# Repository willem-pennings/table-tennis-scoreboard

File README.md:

# Table tennis scoreboard
Hardware and software design for an electronic table tennis score board.

## Features
This device has the following characteristics:
- Keeps track of scores, number of games, and timeouts.
- Remotely controlled using Wi-Fi and a web server.
- A mechanical design which is mainly based on laser-cut parts.
- WS2813 LEDs: adjustable screen colour and brightness.
- Software runs on an ESP32-S3.

## Building it
Mechanical parts are laser-cut from sheet material. An overview of individual parts:
- [Perspex Frost Midnight Black 9221, 3 mm thickness](https://www.laserbeest.nl/materialen/acrylaat-zwart-frost-3mm/)
  - ``front.svg``
  - ``back.svg``
  - ``wall-side-no-holes.svg``
  - ``wall-side-with-holes.svg``
  - ``wall-top-bottom.svg``
- [Perspex Frost Slate Grey 9T23, 3 mm thickness](https://www.laserbeest.nl/materialen/acrylaat-frost-donkergrijs-3-mm/)
  - ``diffuser-major.svg``
  - ``diffuser-minor.svg``
  - ``diffuser-timeout.svg``
- [PE rigid foam, 20 mm thickness](https://snijlab.nl/en/products/pe-rigid-foam?variant=48708138500423)
  - ``lightbox.svg``

Production files have also been prepared which can be sent to Dutch lasercutting companies as-is:
 - ``mechanical/production/production-laserbeest.pdf``
 - ``mechanical/production/production-snijlab.pdf``

The following additional parts are required to assemble the enclosure:
- 50x ISO7380 screw, M3x10.
- 15x M3x50 standoff, fully threaded, black ([example](https://www.aliexpress.com/item/1005004063804402.html)).
- 15x M3x20 standoff, fully threaded ([example](https://www.aliexpress.com/item/4000152799825.html)).
- USB type C extension cable ([example](https://www.aliexpress.com/item/1005005446667716.html)).
- Cyanoacrylate glue to join the frosted diffusers to the front plate.

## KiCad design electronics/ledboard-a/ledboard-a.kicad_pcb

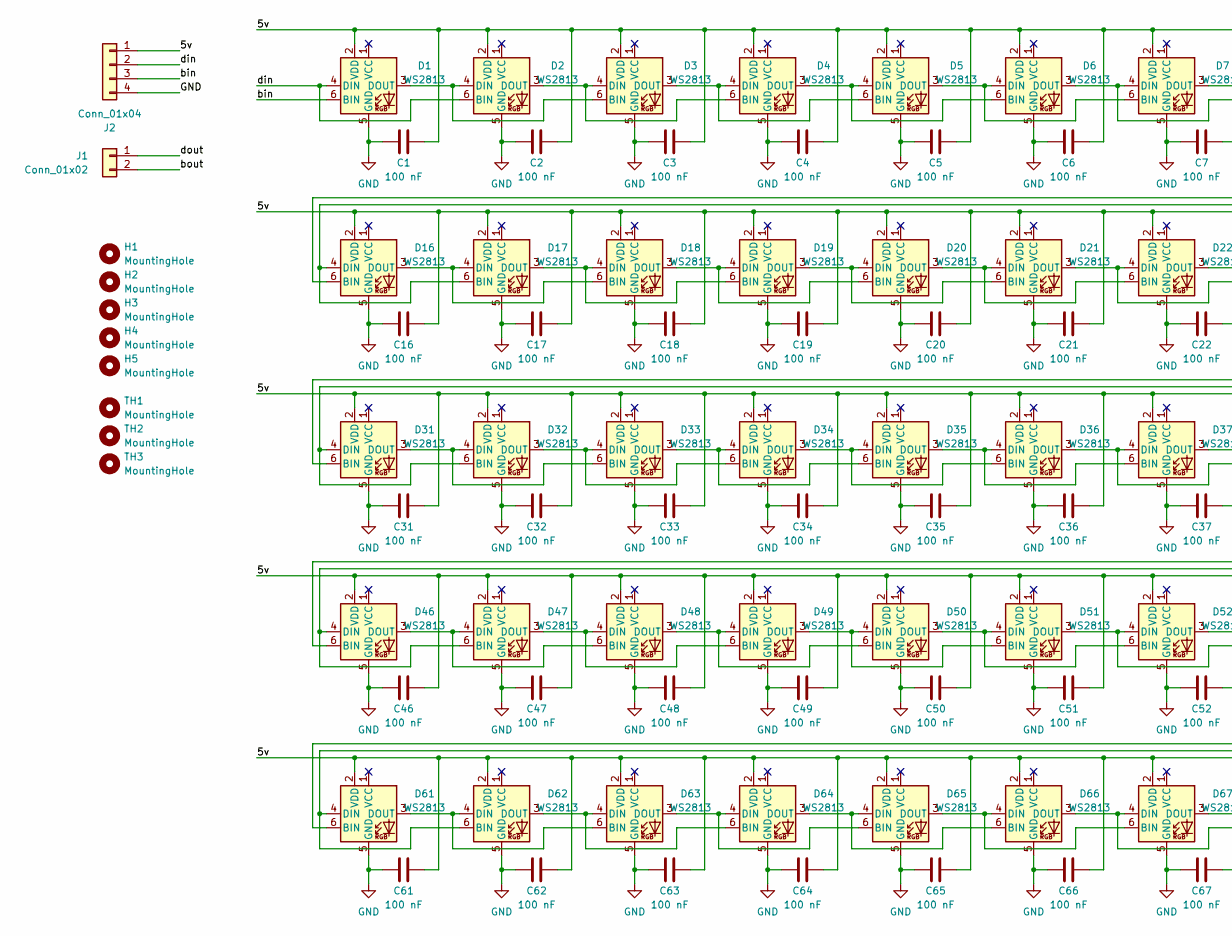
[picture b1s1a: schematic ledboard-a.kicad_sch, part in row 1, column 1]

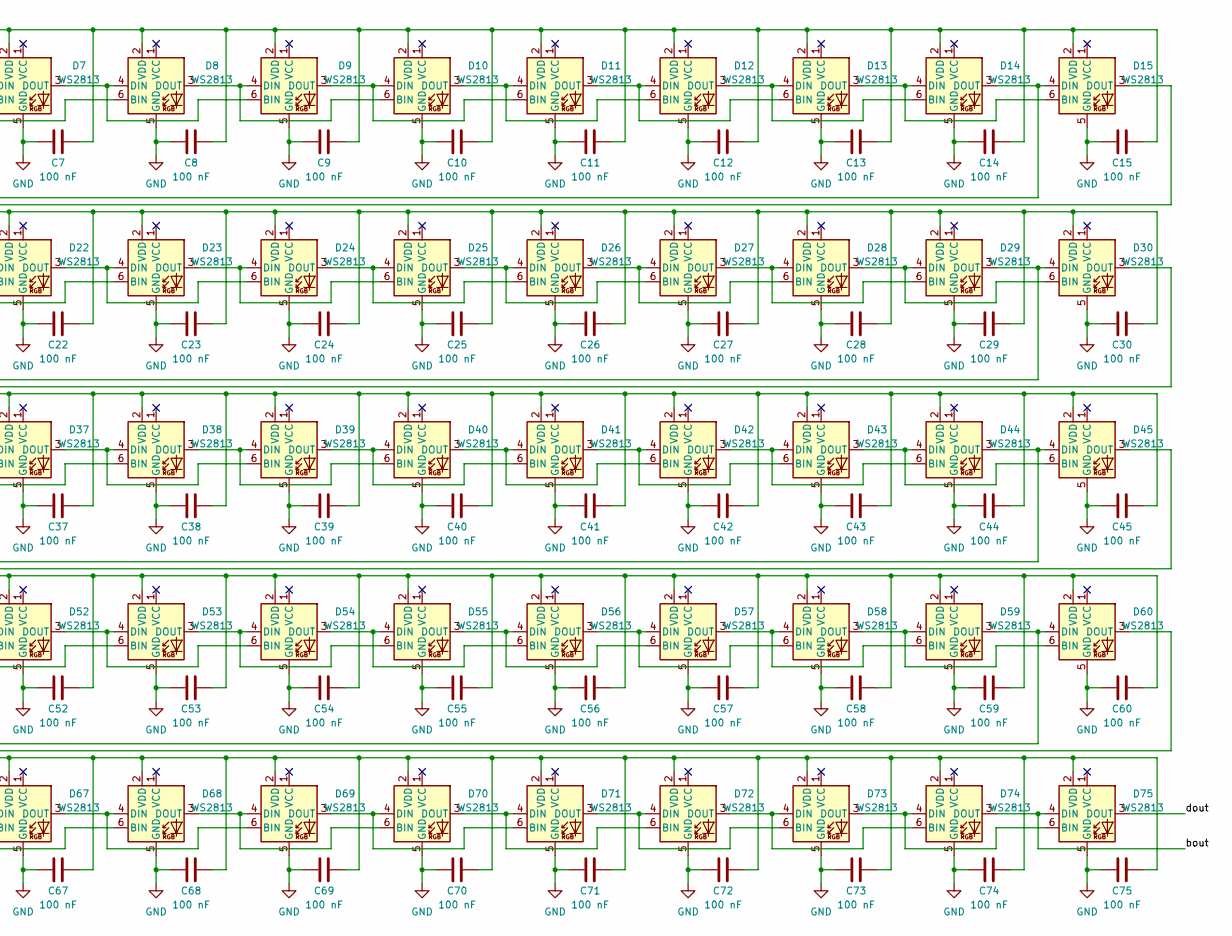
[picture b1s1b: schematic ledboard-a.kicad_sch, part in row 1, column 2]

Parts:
C1, C2, C3, C4, C5, C6, C7, C8, C9, C10, C11, C12, C13, C14, C15, C16, C17, C18, C19, C20, C21, C22, C23, C24, C25, C26, C27, C28, C29, C30, C31, C32, C33, C34, C35, C36, C37, C38, C39, C40, C41, C42, C43, C44, C45, C46, C47, C48, C49, C50, C51, C52, C53, C54, C55, C56, C57, C58, C59, C60, C61, C62, C63, C64, C65, C66, C67, C68, C69, C70, C71, C72, C73, C74, C75: 100 nF; C_0603_1608Metric; LCSC C14663
D1, D2, D3, D4, D5, D6, D7, D8, D9, D10, D11, D12, D13, D14, D15, D16, D17, D18, D19, D20, D21, D22, D23, D24, D25, D26, D27, D28, D29, D30, D31, D32, D33, D34, D35, D36, D37, D38, D39, D40, D41, D42, D43, D44, D45, D46, D47, D48, D49, D50, D51, D52, D53, D54, D55, D56, D57, D58, D59, D60, D61, D62, D63, D64, D65, D66, D67, D68, D69, D70, D71, D72, D73, D74, D75: WS2813; LED_WS2812_PLCC6_5.0x5.0mm_P1.6mm; LCSC C160214
H1, H2, H3, H4, H5: MountingHole; MountingHole_3.2mm_M3_DIN965_Pad
J1: Conn_01x02; Dorabo DB128V-5.08-2P
J2: Conn_01x04; Dorabo DB128V-5.08-4P
TH1, TH2, TH3: MountingHole; JLCPCB tooling hole

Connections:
/5v: C1.2, C2.2, C3.2, C4.2, C5.2, C6.2, C7.2, C8.2, C9.2, C10.2, C11.2, C12.2, C13.2, C14.2, C15.2, C16.2, C17.2, C18.2, C19.2, C20.2, C21.2, C22.2, C23.2, C24.2, C25.2, C26.2, C27.2, C28.2, C29.2, C30.2, C31.2, C32.2, C33.2, C34.2, C35.2, C36.2, C37.2, C38.2, C39.2, C40.2, C41.2, C42.2, C43.2, C44.2, C45.2, C46.2, C47.2, C48.2, C49.2, C50.2, C51.2, C52.2, C53.2, C54.2, C55.2, C56.2, C57.2, C58.2, C59.2, C60.2, C61.2, C62.2, C63.2, C64.2, C65.2, C66.2, C67.2, C68.2, C69.2, C70.2, C71.2, C72.2, C73.2, C74.2, C75.2, D1.2 (VDD), D2.2 (VDD), D3.2 (VDD), D4.2 (VDD), D5.2 (VDD), D6.2 (VDD), D7.2 (VDD), D8.2 (VDD), D9.2 (VDD), D10.2 (VDD), D11.2 (VDD), D12.2 (VDD), D13.2 (VDD), D14.2 (VDD), D15.2 (VDD), D16.2 (VDD), D17.2 (VDD), D18.2 (VDD), D19.2 (VDD), D20.2 (VDD), D21.2 (VDD), D22.2 (VDD), D23.2 (VDD), D24.2 (VDD), D25.2 (VDD), D26.2 (VDD), D27.2 (VDD), D28.2 (VDD), D29.2 (VDD), D30.2 (VDD), D31.2 (VDD), D32.2 (VDD), D33.2 (VDD), D34.2 (VDD), D35.2 (VDD), D36.2 (VDD), D37.2 (VDD), D38.2 (VDD), D39.2 (VDD), D40.2 (VDD), D41.2 (VDD), D42.2 (VDD), D43.2 (VDD), D44.2 (VDD), D45.2 (VDD), D46.2 (VDD), D47.2 (VDD), D48.2 (VDD), D49.2 (VDD), D50.2 (VDD), D51.2 (VDD), D52.2 (VDD), D53.2 (VDD), D54.2 (VDD), D55.2 (VDD), D56.2 (VDD), D57.2 (VDD), D58.2 (VDD), D59.2 (VDD), D60.2 (VDD), D61.2 (VDD), D62.2 (VDD), D63.2 (VDD), D64.2 (VDD), D65.2 (VDD), D66.2 (VDD), D67.2 (VDD), D68.2 (VDD), D69.2 (VDD), D70.2 (VDD), D71.2 (VDD), D72.2 (VDD), D73.2 (VDD), D74.2 (VDD), D75.2 (VDD), J2.1
/bin: D1.6 (BIN), J2.3
/bout: D74.3 (DOUT), D75.4 (DIN), J1.2
/din: D1.4 (DIN), D2.6 (BIN), J2.2
/dout: D75.3 (DOUT), J1.1
GND: C1.1, C2.1, C3.1, C4.1, C5.1, C6.1, C7.1, C8.1, C9.1, C10.1, C11.1, C12.1, C13.1, C14.1, C15.1, C16.1, C17.1, C18.1, C19.1, C20.1, C21.1, C22.1, C23.1, C24.1, C25.1, C26.1, C27.1, C28.1, C29.1, C30.1, C31.1, C32.1, C33.1, C34.1, C35.1, C36.1, C37.1, C38.1, C39.1, C40.1, C41.1, C42.1, C43.1, C44.1, C45.1, C46.1, C47.1, C48.1, C49.1, C50.1, C51.1, C52.1, C53.1, C54.1, C55.1, C56.1, C57.1, C58.1, C59.1, C60.1, C61.1, C62.1, C63.1, C64.1, C65.1, C66.1, C67.1, C68.1, C69.1, C70.1, C71.1, C72.1, C73.1, C74.1, C75.1, D1.5 (GND), D2.5 (GND), D3.5 (GND), D4.5 (GND), D5.5 (GND), D6.5 (GND), D7.5 (GND), D8.5 (GND), D9.5 (GND), D10.5 (GND), D11.5 (GND), D12.5 (GND), D13.5 (GND), D14.5 (GND), D15.5 (GND), D16.5 (GND), D17.5 (GND), D18.5 (GND), D19.5 (GND), D20.5 (GND), D21.5 (GND), D22.5 (GND), D23.5 (GND), D24.5 (GND), D25.5 (GND), D26.5 (GND), D27.5 (GND), D28.5 (GND), D29.5 (GND), D30.5 (GND), D31.5 (GND), D32.5 (GND), D33.5 (GND), D34.5 (GND), D35.5 (GND), D36.5 (GND), D37.5 (GND), D38.5 (GND), D39.5 (GND), D40.5 (GND), D41.5 (GND), D42.5 (GND), D43.5 (GND), D44.5 (GND), D45.5 (GND), D46.5 (GND), D47.5 (GND), D48.5 (GND), D49.5 (GND), D50.5 (GND), D51.5 (GND), D52.5 (GND), D53.5 (GND), D54.5 (GND), D55.5 (GND), D56.5 (GND), D57.5 (GND), D58.5 (GND), D59.5 (GND), D60.5 (GND), D61.5 (GND), D62.5 (GND), D63.5 (GND), D64.5 (GND), D65.5 (GND), D66.5 (GND), D67.5 (GND), D68.5 (GND), D69.5 (GND), D70.5 (GND), D71.5 (GND), D72.5 (GND), D73.5 (GND), D74.5 (GND), D75.5 (GND), J2.4
unnamed: D1.3 (DOUT), D2.4 (DIN), D3.6 (BIN)
unnamed: D2.3 (DOUT), D3.4 (DIN), D4.6 (BIN)
unnamed: D3.3 (DOUT), D4.4 (DIN), D5.6 (BIN)
unnamed: D4.3 (DOUT), D5.4 (DIN), D6.6 (BIN)
unnamed: D5.3 (DOUT), D6.4 (DIN), D7.6 (BIN)
unnamed: D6.3 (DOUT), D7.4 (DIN), D8.6 (BIN)
unnamed: D7.3 (DOUT), D8.4 (DIN), D9.6 (BIN)
unnamed: D8.3 (DOUT), D9.4 (DIN), D10.6 (BIN)
unnamed: D9.3 (DOUT), D10.4 (DIN), D11.6 (BIN)
unnamed: D10.3 (DOUT), D11.4 (DIN), D12.6 (BIN)
unnamed: D11.3 (DOUT), D12.4 (DIN), D13.6 (BIN)
unnamed: D12.3 (DOUT), D13.4 (DIN), D14.6 (BIN)
unnamed: D13.3 (DOUT), D14.4 (DIN), D15.6 (BIN)
unnamed: D14.3 (DOUT), D15.4 (DIN), D16.6 (BIN)
unnamed: D15.3 (DOUT), D16.4 (DIN), D17.6 (BIN)
unnamed: D16.3 (DOUT), D17.4 (DIN), D18.6 (BIN)
unnamed: D17.3 (DOUT), D18.4 (DIN), D19.6 (BIN)
unnamed: D18.3 (DOUT), D19.4 (DIN), D20.6 (BIN)
unnamed: D19.3 (DOUT), D20.4 (DIN), D21.6 (BIN)
unnamed: D20.3 (DOUT), D21.4 (DIN), D22.6 (BIN)
unnamed: D21.3 (DOUT), D22.4 (DIN), D23.6 (BIN)
unnamed: D22.3 (DOUT), D23.4 (DIN), D24.6 (BIN)
unnamed: D23.3 (DOUT), D24.4 (DIN), D25.6 (BIN)
unnamed: D24.3 (DOUT), D25.4 (DIN), D26.6 (BIN)
unnamed: D25.3 (DOUT), D26.4 (DIN), D27.6 (BIN)
unnamed: D26.3 (DOUT), D27.4 (DIN), D28.6 (BIN)
unnamed: D27.3 (DOUT), D28.4 (DIN), D29.6 (BIN)
unnamed: D28.3 (DOUT), D29.4 (DIN), D30.6 (BIN)
unnamed: D29.3 (DOUT), D30.4 (DIN), D31.6 (BIN)
unnamed: D30.3 (DOUT), D31.4 (DIN), D32.6 (BIN)
unnamed: D31.3 (DOUT), D32.4 (DIN), D33.6 (BIN)
unnamed: D32.3 (DOUT), D33.4 (DIN), D34.6 (BIN)
unnamed: D33.3 (DOUT), D34.4 (DIN), D35.6 (BIN)
unnamed: D34.3 (DOUT), D35.4 (DIN), D36.6 (BIN)
unnamed: D35.3 (DOUT), D36.4 (DIN), D37.6 (BIN)
unnamed: D36.3 (DOUT), D37.4 (DIN), D38.6 (BIN)
unnamed: D37.3 (DOUT), D38.4 (DIN), D39.6 (BIN)
unnamed: D38.3 (DOUT), D39.4 (DIN), D40.6 (BIN)
unnamed: D39.3 (DOUT), D40.4 (DIN), D41.6 (BIN)
unnamed: D40.3 (DOUT), D41.4 (DIN), D42.6 (BIN)
unnamed: D41.3 (DOUT), D42.4 (DIN), D43.6 (BIN)
unnamed: D42.3 (DOUT), D43.4 (DIN), D44.6 (BIN)
unnamed: D43.3 (DOUT), D44.4 (DIN), D45.6 (BIN)
unnamed: D44.3 (DOUT), D45.4 (DIN), D46.6 (BIN)
unnamed: D45.3 (DOUT), D46.4 (DIN), D47.6 (BIN)
unnamed: D46.3 (DOUT), D47.4 (DIN), D48.6 (BIN)
unnamed: D47.3 (DOUT), D48.4 (DIN), D49.6 (BIN)
unnamed: D48.3 (DOUT), D49.4 (DIN), D50.6 (BIN)
unnamed: D49.3 (DOUT), D50.4 (DIN), D51.6 (BIN)
unnamed: D50.3 (DOUT), D51.4 (DIN), D52.6 (BIN)
unnamed: D51.3 (DOUT), D52.4 (DIN), D53.6 (BIN)
unnamed: D52.3 (DOUT), D53.4 (DIN), D54.6 (BIN)
unnamed: D53.3 (DOUT), D54.4 (DIN), D55.6 (BIN)
unnamed: D54.3 (DOUT), D55.4 (DIN), D56.6 (BIN)
unnamed: D55.3 (DOUT), D56.4 (DIN), D57.6 (BIN)
unnamed: D56.3 (DOUT), D57.4 (DIN), D58.6 (BIN)
unnamed: D57.3 (DOUT), D58.4 (DIN), D59.6 (BIN)
unnamed: D58.3 (DOUT), D59.4 (DIN), D60.6 (BIN)
unnamed: D59.3 (DOUT), D60.4 (DIN), D61.6 (BIN)
unnamed: D60.3 (DOUT), D61.4 (DIN), D62.6 (BIN)
unnamed: D61.3 (DOUT), D62.4 (DIN), D63.6 (BIN)
unnamed: D62.3 (DOUT), D63.4 (DIN), D64.6 (BIN)
unnamed: D63.3 (DOUT), D64.4 (DIN), D65.6 (BIN)
unnamed: D64.3 (DOUT), D65.4 (DIN), D66.6 (BIN)
unnamed: D65.3 (DOUT), D66.4 (DIN), D67.6 (BIN)
unnamed: D66.3 (DOUT), D67.4 (DIN), D68.6 (BIN)
unnamed: D67.3 (DOUT), D68.4 (DIN), D69.6 (BIN)
unnamed: D68.3 (DOUT), D69.4 (DIN), D70.6 (BIN)
unnamed: D69.3 (DOUT), D70.4 (DIN), D71.6 (BIN)
unnamed: D70.3 (DOUT), D71.4 (DIN), D72.6 (BIN)
unnamed: D71.3 (DOUT), D72.4 (DIN), D73.6 (BIN)
unnamed: D72.3 (DOUT), D73.4 (DIN), D74.6 (BIN)
unnamed: D73.3 (DOUT), D74.4 (DIN), D75.6 (BIN)

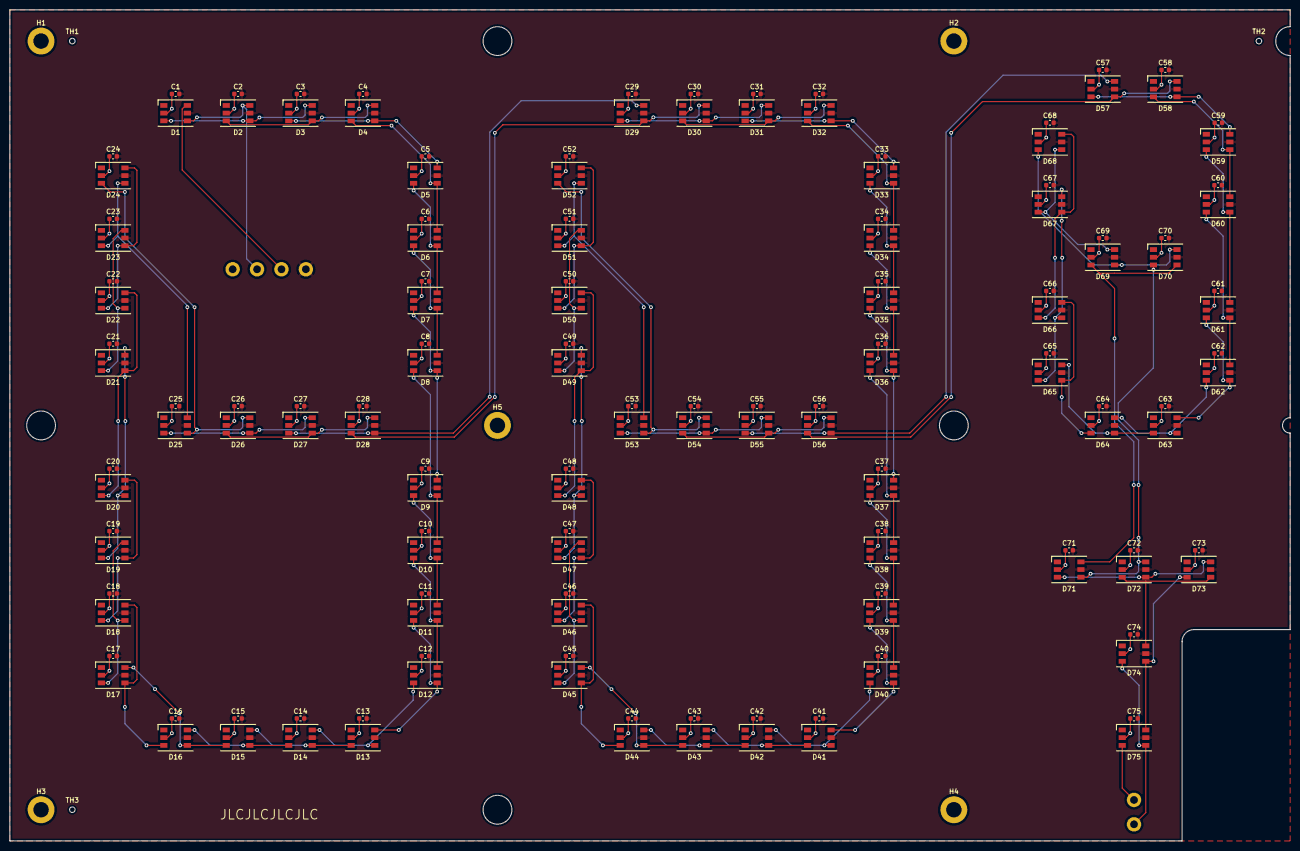
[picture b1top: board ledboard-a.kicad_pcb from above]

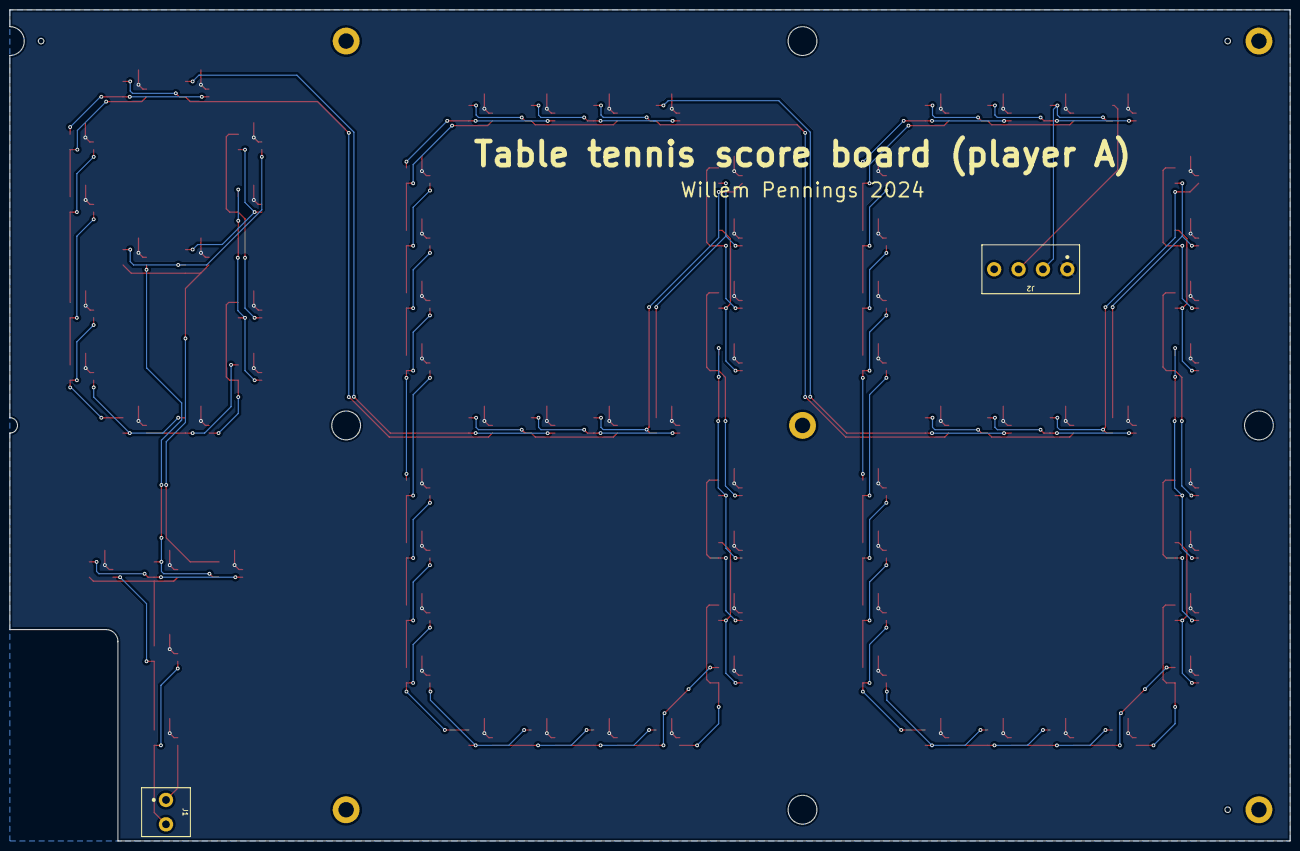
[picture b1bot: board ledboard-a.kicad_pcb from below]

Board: 2 copper layers, 266.5 x 173.0 mm, 160 parts (2 on the bottom side), 79 nets.

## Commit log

2025-02-16 Add missing period
